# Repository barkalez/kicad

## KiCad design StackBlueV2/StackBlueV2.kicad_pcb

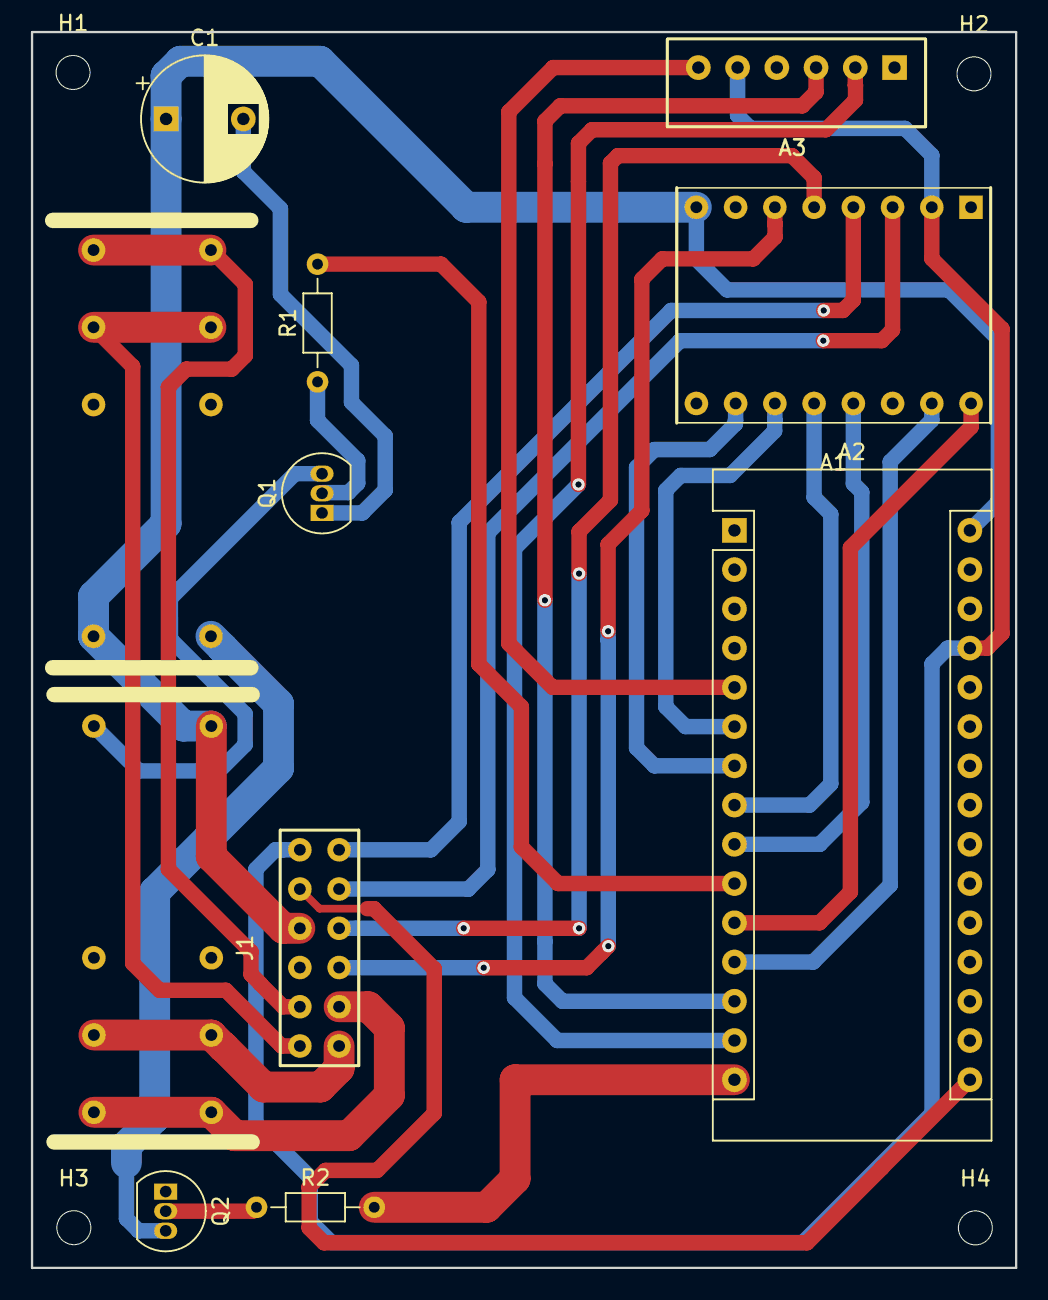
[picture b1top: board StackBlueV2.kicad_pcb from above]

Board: 2 copper layers, 63.7 x 80.0 mm, 15 parts (0 on the bottom side), 27 nets.

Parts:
A1: A4988
A2: Arduino_Nano_v3.x; Arduino_Nano
A3: HC-05
C1: C; CP_Radial_D8.0mm_P5.00mm
H1, H2, H3, H4: MountingHole; MountingHole_2.2mm_M2
J1: Conn_02x06_Counter_Clockwise; 2x16 2.54
K1, K2: SMIH-12VDC-SL-C
Q1, Q2: 2N3904; TO-92_Inline
R1, R2: R; R_Axial_DIN0204_L3.6mm_D1.6mm_P7.62mm_Horizontal

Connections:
/1A: A1.4, J1.1
/1B: A1.3, J1.2
/2A: A1.5, J1.3
/2B: A1.6, J1.4
/COLECT_CAM: K1.2, Q2.3
/COLECT_FLASH: K2.2, Q1.3
/DIR_D8: A1.16, A2.11
/ENDSTOP_D13: A2.16, J1.11
/ENHC05_D2: A2.5, A3.6
/GND: A1.1, A1.7, A2.4, A2.29, A3.4, C1.2, J1.9, Q1.1, Q2.1
/MS1_D4: A1.10, A2.7
/MS2_D3: A1.11, A2.6
/MS3_D5: A1.12, A2.8
/RST_D6: A1.13, A1.14, A2.9
/RTN_CAM: J1.8, K1.5, K1.6
/RTN_FLASH: J1.6, K2.5, K2.6
/RXD_D11: A2.14, A3.2
/SHUTTERCAM: J1.7, K1.7, K1.8
/SHUTTERCAM_D12: A2.15, R2.2
/SHUTTERFLASH: J1.5, K2.7, K2.8
/SHUTTERFLASH_D7: A2.10, R1.2
/STEP_D9: A1.15, A2.12
/TXD_D10: A2.13, A3.3
/VCC: A1.2, A2.27, A3.5, J1.12
/VDD: A1.8, A2.30, C1.1, J1.10, K1.1, K2.1
unnamed: Q1.2, R1.1
unnamed: Q2.2, R2.1

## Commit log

2019-06-03 Casi terminado
